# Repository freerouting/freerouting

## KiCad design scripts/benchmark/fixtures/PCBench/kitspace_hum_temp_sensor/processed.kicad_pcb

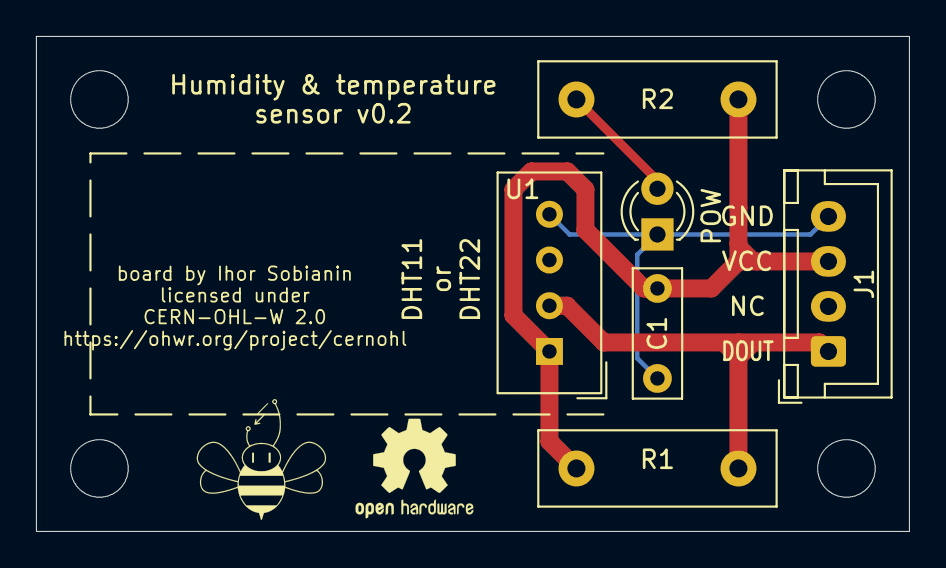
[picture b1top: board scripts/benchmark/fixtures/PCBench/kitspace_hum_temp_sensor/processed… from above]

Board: 2 copper layers, 48.5 x 27.5 mm, 6 parts (0 on the bottom side), 4 nets.

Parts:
C1: 100nF; C_Disc_D7.0mm_W2.5mm_P5.00mm
D1: LED; LED_D3.0mm
J1: Conn_01x04; JST_XH_B4B-XH-A_1x04_P2.50mm_Vertical
R1: 5,1k; R_Box_L13.0mm_W4.0mm_P9.00mm
R2: 220; R_Box_L13.0mm_W4.0mm_P9.00mm
U1: DHT11; Aosong_DHT11_5.5x12.0_P2.54mm

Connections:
+5V: C1.1, J1.3, R1.1, R2.1, U1.1
GND: C1.2, D1.1, J1.4, U1.4
unnamed: D1.2, R2.2
unnamed: J1.1, R1.2, U1.2

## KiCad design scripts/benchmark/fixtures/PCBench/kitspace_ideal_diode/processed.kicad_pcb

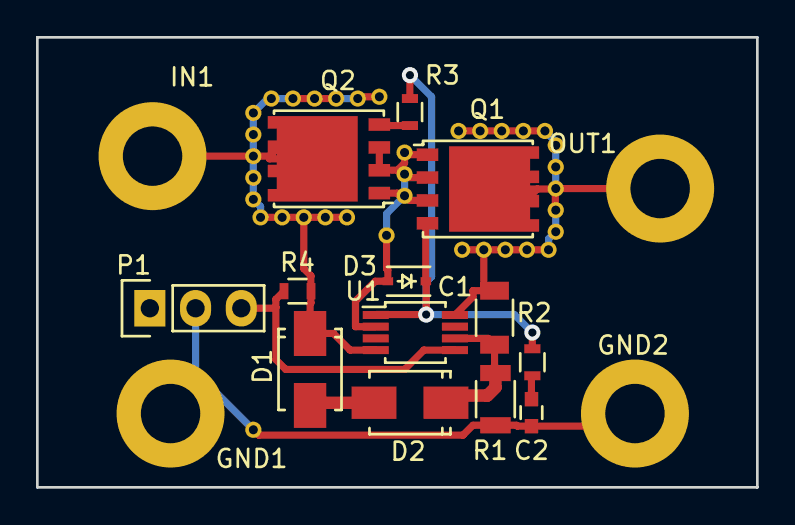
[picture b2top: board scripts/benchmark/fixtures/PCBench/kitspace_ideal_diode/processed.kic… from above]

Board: 2 copper layers, 40.0 x 25.0 mm, 54 parts (0 on the bottom side), 10 nets.

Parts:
C1: 2u2; C_1206
C2: 10n; C_0603
D1: SMAJ60A; SMA_Standard
D2: SMAJ24A; SMA_Standard
D3: MM3Z16VT1; SOD-323
GND1, GND2: CONN_01X01; SolderWirePad_single_2-5mmDrill
IN1: CONN_01X01; SolderWirePad_single_2-5mmDrill
Noname_1: Symbol_OSHW-Logo_SilkScreen
Noname_2, Noname_3, Noname_4, Noname_5, Noname_6, Noname_7, Noname_8, Noname_9, Noname_10, Noname_11, Noname_12, Noname_13, Noname_14, Noname_15, Noname_16, Noname_17, Noname_18, Noname_19, Noname_20, Noname_21, Noname_22, Noname_23, Noname_24, Noname_25, Noname_26, Noname_27, Noname_28, Noname_29, Noname_30, Noname_31, Noname_32, Noname_33, Noname_34, Noname_35, Noname_36, Noname_37: via_0-9_0-5mm
OUT1: CONN_01X01; SolderWirePad_single_2-5mmDrill
P1: CONN_01X03; Pin_Header_Straight_1x03
Q1, Q2: BSC028N06NS; TDSON-8-1
R1: 3k6; R_1206
R2: 10k; R_0603
R3: 10R; R_0603
R4: 1M; R_0603
U1: LTC4359; MSOP-8_3x3mm_Pitch0.65mm

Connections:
/GATE: D3.1, Q1.4, R2.1, R3.2, U1.1
/IN: D1.1, IN1.1, Noname_14.1, Noname_20.1, Noname_21.1, Noname_22.1, Noname_23.1, Noname_24.1, Noname_25.1, Noname_26.1, Noname_27.1, Noname_28.1, Noname_29.1, Noname_30.1, Noname_31.1, Noname_32.1, Noname_33.1, Noname_34.1, Q2.5, Q2.6, Q2.7, Q2.8, R4.1, U1.4
/OUT: C1.1, Noname_2.1, Noname_3.1, Noname_4.1, Noname_5.1, Noname_6.1, Noname_7.1, Noname_8.1, Noname_9.1, Noname_10.1, Noname_11.1, Noname_12.1, Noname_16.1, Noname_17.1, Noname_18.1, Noname_19.1, OUT1.1, Q1.5, Q1.6, Q1.7, Q1.8, U1.8
/SOURCE: D3.2, Noname_15.1, Noname_35.1, Noname_36.1, Noname_37.1, Q1.1, Q1.2, Q1.3, Q2.1, Q2.2, Q2.3, U1.2
/VSS: C1.2, D2.1, R1.1, U1.6
/~SHDN: P1.3, R4.2, U1.5
GND: C2.2, GND1.1, GND2.1, Noname_13.1, P1.2, R1.2
unnamed: C2.1, R2.2
unnamed: D1.2, D2.2
unnamed: Q2.4, R3.1

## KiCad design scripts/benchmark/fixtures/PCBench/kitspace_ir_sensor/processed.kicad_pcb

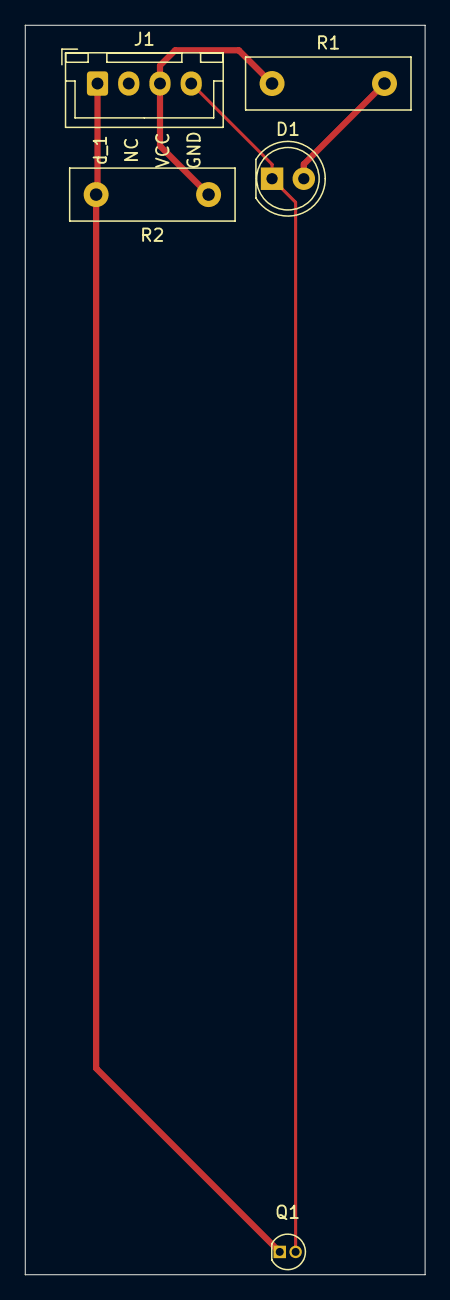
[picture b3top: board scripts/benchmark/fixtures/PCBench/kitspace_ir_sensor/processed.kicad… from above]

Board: 2 copper layers, 32.0 x 100.0 mm, 5 parts (0 on the bottom side), 4 nets.

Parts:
D1: LED; LED_D5.0mm
J1: Conn_01x04; JST_XH_B4B-XH-A_1x04_P2.50mm_Vertical
Q1: Q_Photo_NPN; OP505A
R1: 47; R_Box_L13.0mm_W4.0mm_P9.00mm
R2: 10k; R_Box_L13.0mm_W4.0mm_P9.00mm

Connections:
+5V: J1.3, R1.1, R2.1
GND: D1.1, J1.4, Q1.2
unnamed: D1.2, R1.2
data: J1.1, Q1.1, R2.2

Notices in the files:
scripts/benchmark/fixtures/PCBench/kitspace_hum_temp_sensor/processed.kicad_pcb:
licensed under
CERN-OHL-W 2.0
